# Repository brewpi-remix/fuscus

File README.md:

# 

# A BrewPi Remix Fork of Fuscus

Fuscus is the Latin name for the Brown Water-Python.  It is also the name
[Andrew Errington](https://github.com/andrewerrington) chose for this
native Python implementation of the BrewPi fermentation controller.  Why
did he choose it?  I forget but it's buried in the [original thread](https://www.homebrewtalk.com/threads/native-python-brewpi-controller.575724/) somewhere I'm sure.

The [original project](https://github.com/andrewerrington/fuscus) was forked
to BrewPi Remix in order to allow the use of a Raspberry Pi within that
ecosystem.  Andrew's repo has not been updated since November 18th, 2016;
it's fair to say he's done with what he wanted to do.

## Does it work?

Let me say I don't think using a Pi for critical temperature control is
a good idea.  Having said that, here is what Andrew shared originally:

> There are very good reasons for allocating a microcontroller to the
task of heating and cooling control.  The primary one being that they
are very reliable.  If the Raspberry Pi should crash the microcontroller
will continue to monitor and maintain the last set temperature.  If
the control is done by the Pi then it could crash and leave the heater
or cooler stuck on, which will ruin the fermentation.
>
> Despite the possible risks of failure this project re-implements
the Arduino control code (v0.2.11) in Python so that it can run natively on
the Pi.  The other BrewPi components will
talk to this Python code as if it were an Arduino, so they can be be used
unchanged.  Hardware that was connected to the Arduino, such as 1-wire
temperature sensors, an LCD, and relays for the heater and cooler are
connected to the Pi GPIO pins.

Does this mean BrewPi Remix supports Fuscus?  Not at this time (3/19/21)
but it obviously means I'm playing around with it.

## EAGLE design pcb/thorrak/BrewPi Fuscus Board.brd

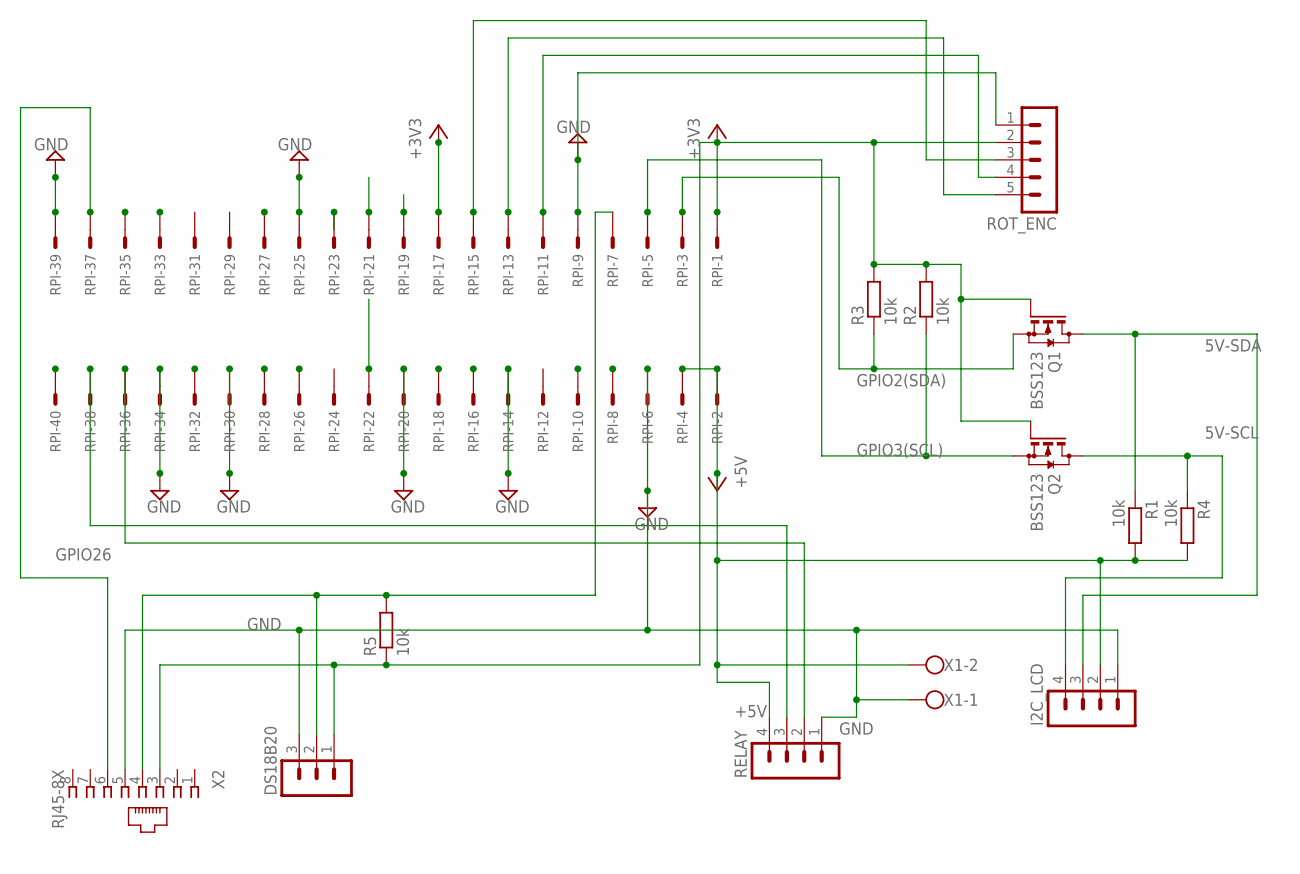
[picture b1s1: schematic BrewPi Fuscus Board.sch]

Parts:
DS18B20: MA03-1
I2C_LCD: MA04-1
Q1, Q2: BSS123; SOT23
R1, R2, R3, R4, R5: 10k; M1206
RELAY: MA04-1
ROT_ENC: MA05-1
RPI: 057-040-1
X1: W237-102
X2: RJ45-8X; RJ45-NO-SHIELD

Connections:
5V-SCL: I2C_LCD.4, Q2.3 (D), R4.1
5V-SDA: I2C_LCD.3, Q1.3 (D), R1.1
+3V3: DS18B20.1, Q1.1 (G), Q2.1 (G), R2.2, R3.2, R5.1, ROT_ENC.2, RPI.1, RPI.17, X2.3
+5V: I2C_LCD.2, R1.2, R4.2, RELAY.4, RPI.2, RPI.4, X1.2
GND: DS18B20.3, I2C_LCD.1, RELAY.1, ROT_ENC.1, RPI.6, RPI.9, RPI.14, RPI.20, RPI.25, RPI.30, RPI.34, RPI.39, X1.1, X2.5
GPIO2(SDA): Q1.2 (S), R3.1, RPI.3
GPIO3(SCL): Q2.2 (S), R2.1, RPI.5
GPIO7(SPI_CE1_N): RPI.26
GPIO9(SPI_MISO): RPI.21
GPIO10(SPI_MOSI): RPI.19
GPIO11(SPI_SCLK): RPI.23
GPIO12: RPI.32
GPIO13: RPI.33
GPIO14(TXD0): RPI.8
GPIO15(RXD0): RPI.10
GPIO16: RELAY.2, RPI.36
GPIO17(GPIO_GEN0): ROT_ENC.4, RPI.11
GPIO19: RPI.35
GPIO20: RELAY.3, RPI.38
GPIO21: RPI.40
GPIO22(GPIO_GEN3): ROT_ENC.3, RPI.15
GPIO23(GPIO_GEN4): RPI.16
GPIO24(GPIO_GEN5): RPI.18
GPIO26: RPI.37, X2.6
GPIO27(GPIO_GEN2): ROT_ENC.5, RPI.13
ID_SC: RPI.28
ID_SD: RPI.27
unnamed: DS18B20.2, R5.2, RPI.7, X2.4
RST: RPI.22

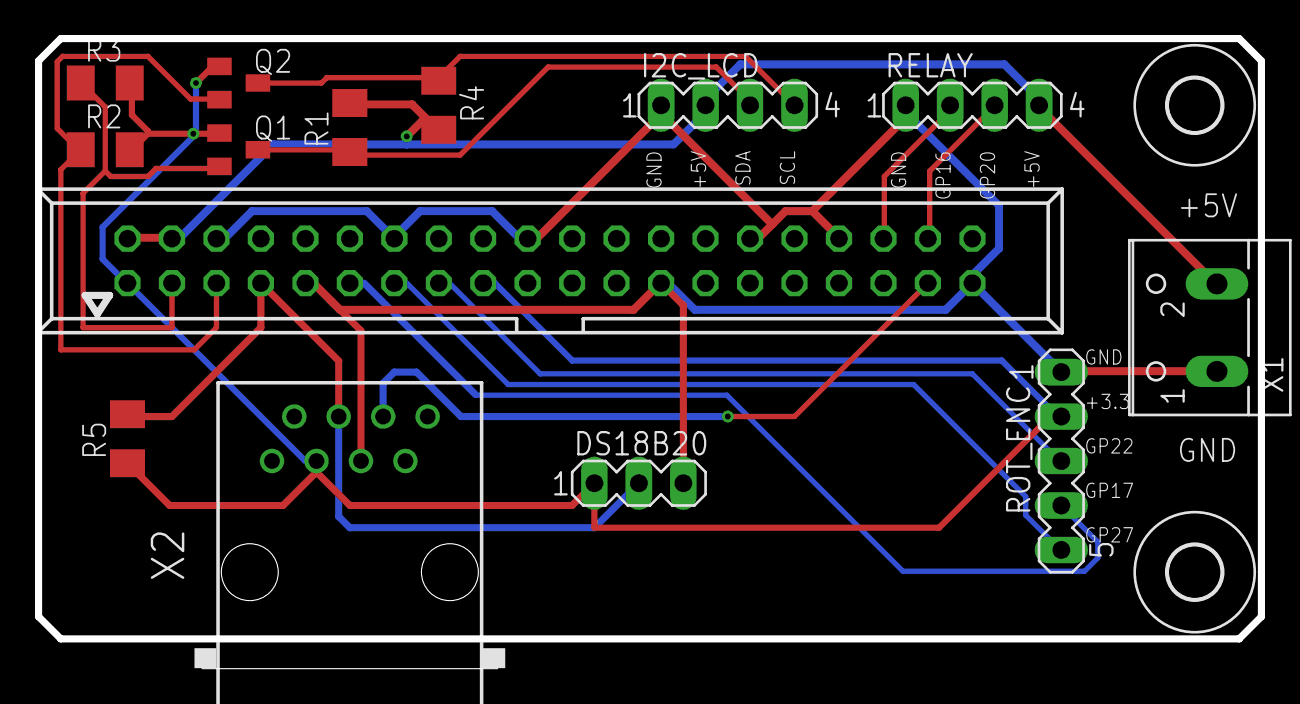
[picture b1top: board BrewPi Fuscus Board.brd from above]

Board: 2 copper layers, 69.9 x 35.8 mm, 16 parts (0 on the bottom side), 14 nets.

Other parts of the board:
U$3, U$4: 3,0

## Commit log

2021-03-19 Add Thorrak's original board design
2021-03-19 Explain the fork

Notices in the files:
README.md:
License: GPL v3
